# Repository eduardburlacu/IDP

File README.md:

# IDP

## Dimensions
- Truck Height: 95mm
- Tunnel Width: 345mm
- Tunnel Length: 510mm
-

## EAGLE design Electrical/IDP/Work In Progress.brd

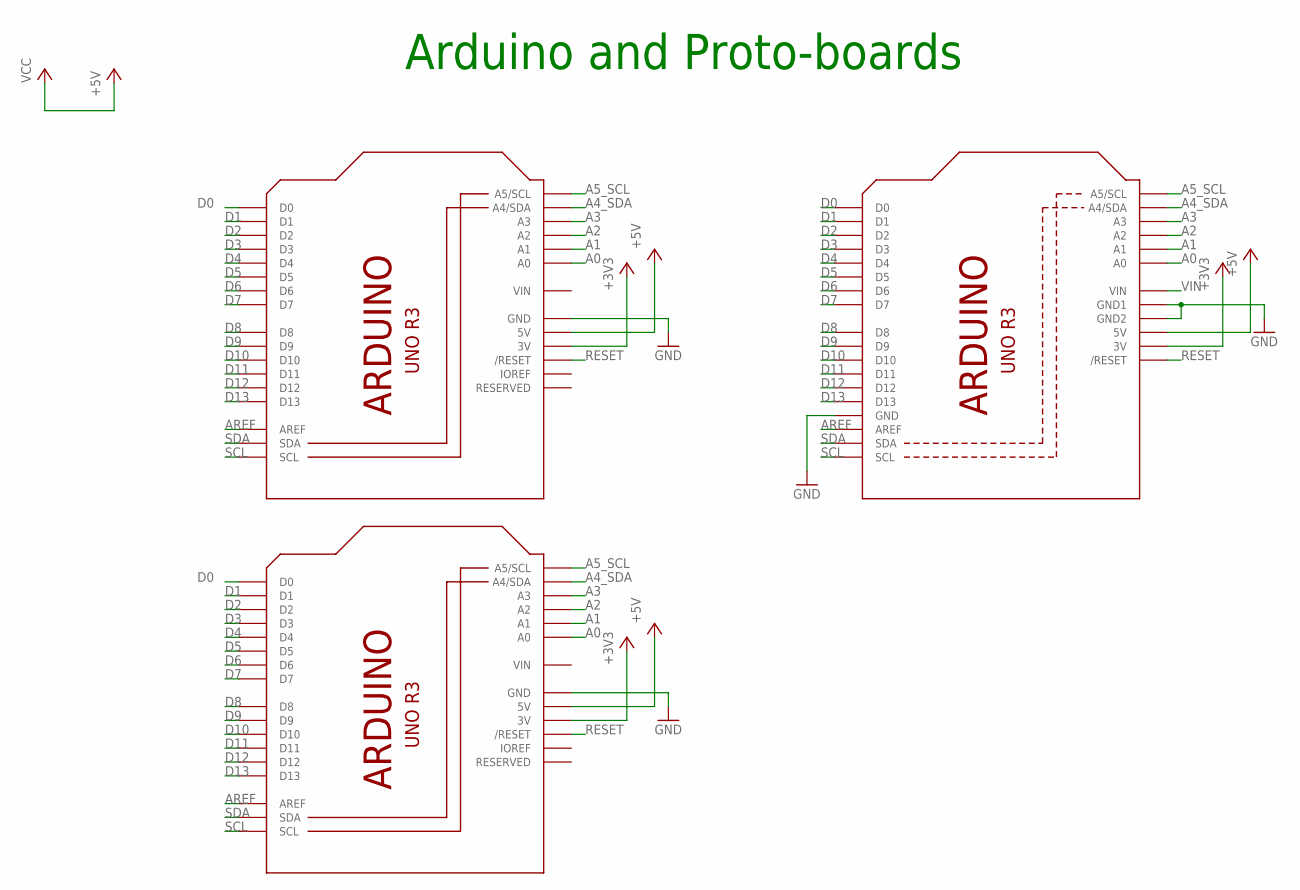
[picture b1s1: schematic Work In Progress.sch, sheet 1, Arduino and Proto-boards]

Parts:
M1, M2: IDP_PROTOBOARD_LARGE_LARGE; IDP_PROTO_LARGE
Q1: ARDUINOR3-NOIOREF-NOTEXT; ARDUINOR3-NOTEXT-NOIOREF

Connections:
+3V3: M1.3V, M2.3V, Q1.3V
+5V: M1.5V, M1.5V@0 (5V), M1.5V@1 (5V), M1.5V@2 (5V), M1.5V@3 (5V), M1.5V@4 (5V), M1.5V@5 (5V), M1.5V@6 (5V), M1.5V@7 (5V), M1.5V@8 (5V), M1.5V@9 (5V), M1.5V@10 (5V), M1.5V@11 (5V), M1.5V@12 (5V), M1.5V@13 (5V), M1.5V@14 (5V), M1.5V@15 (5V), M1.5V@16 (5V), M1.5V@17 (5V), M1.5V@18 (5V), M1.5V@19 (5V), M1.5V@20 (5V), M1.5V@21 (5V), M1.5V@22 (5V), M1.5V@23 (5V), M1.5V@24 (5V), M1.5V@25 (5V), M1.5V@26 (5V), M1.5V@27 (5V), M1.5V@28 (5V), M1.5V@29 (5V), M1.5V@30 (5V), M1.5V@31 (5V), M1.5V@32 (5V), M1.5V@33 (5V), M1.5V@34 (5V), M1.5V@35 (5V), M1.5V@36 (5V), M1.5V@37 (5V), M1.5V@38 (5V), M1.5V@39 (5V), M1.5V@40 (5V), M1.5V@41 (5V), M1.5V@42 (5V), M1.5V@43 (5V), M1.5V@44 (5V), M1.5V@45 (5V), M1.5V@46 (5V), M1.5V@47 (5V), M1.5V@48 (5V), M1.5V@49 (5V), M1.5V@50 (5V), M1.5V@51 (5V), M1.5V@52 (5V), M1.5V@53 (5V), M1.5V@54 (5V), M1.5V@55 (5V), M1.5V@56 (5V), M1.5V@57 (5V), M1.5V@58 (5V), M1.5V@59 (5V), M1.5V@60 (5V), M1.5V@61 (5V), M1.5V@62 (5V), M1.5V@63 (5V), M1.5V@64 (5V), M1.5V@65 (5V), M1.5V@66 (5V), M1.5V@67 (5V), M1.5V@68 (5V), M1.5V@69 (5V), M1.5V@70 (5V), M2.5V, M2.5V@0 (5V), M2.5V@1 (5V), M2.5V@2 (5V), M2.5V@3 (5V), M2.5V@4 (5V), M2.5V@5 (5V), M2.5V@6 (5V), M2.5V@7 (5V), M2.5V@8 (5V), M2.5V@9 (5V), M2.5V@10 (5V), M2.5V@11 (5V), M2.5V@12 (5V), M2.5V@13 (5V), M2.5V@14 (5V), M2.5V@15 (5V), M2.5V@16 (5V), M2.5V@17 (5V), M2.5V@18 (5V), M2.5V@19 (5V), M2.5V@20 (5V), M2.5V@21 (5V), M2.5V@22 (5V), M2.5V@23 (5V), M2.5V@24 (5V), M2.5V@25 (5V), M2.5V@26 (5V), M2.5V@27 (5V), M2.5V@28 (5V), M2.5V@29 (5V), M2.5V@30 (5V), M2.5V@31 (5V), M2.5V@32 (5V), M2.5V@33 (5V), M2.5V@34 (5V), M2.5V@35 (5V), M2.5V@36 (5V), M2.5V@37 (5V), M2.5V@38 (5V), M2.5V@39 (5V), M2.5V@40 (5V), M2.5V@41 (5V), M2.5V@42 (5V), M2.5V@43 (5V), M2.5V@44 (5V), M2.5V@45 (5V), M2.5V@46 (5V), M2.5V@47 (5V), M2.5V@48 (5V), M2.5V@49 (5V), M2.5V@50 (5V), M2.5V@51 (5V), M2.5V@52 (5V), M2.5V@53 (5V), M2.5V@54 (5V), M2.5V@55 (5V), M2.5V@56 (5V), M2.5V@57 (5V), M2.5V@58 (5V), M2.5V@59 (5V), M2.5V@60 (5V), M2.5V@61 (5V), M2.5V@62 (5V), M2.5V@63 (5V), M2.5V@64 (5V), M2.5V@65 (5V), M2.5V@66 (5V), M2.5V@67 (5V), M2.5V@68 (5V), M2.5V@69 (5V), M2.5V@70 (5V), Q1.5V; also elsewhere on the board
A0: M1.A0, M2.A0, Q1.A0
A1: M1.A1, M2.A1, Q1.A1
A2: M1.A2, M2.A2, Q1.A2
A3: M1.A3, M2.A3, Q1.A3
A4_SDA: M1.A4 (A4/SDA), M2.A4 (A4/SDA), Q1.A4 (A4/SDA)
A5_SCL: M1.A5 (A5/SCL), M2.A5 (A5/SCL), Q1.A5 (A5/SCL)
AREF: M1.AREF, M2.AREF, Q1.AREF
D0: M1.D0, M2.D0, Q1.D0
D1: M1.D1, M2.D1, Q1.D1; also elsewhere on the board
D2: M1.D2, M2.D2, Q1.D2; also elsewhere on the board
D3: M1.D3, M2.D3, Q1.D3; also elsewhere on the board
D4: M1.D4, M2.D4, Q1.D4; also elsewhere on the board
D5: M1.D5, M2.D5, Q1.D5
D6: M1.D6, M2.D6, Q1.D6
D7: M1.D7, M2.D7, Q1.D7
D8: M1.D8, M2.D8, Q1.D8; also elsewhere on the board
D9: M1.D9, M2.D9, Q1.D9; also elsewhere on the board
D10: M1.D10, M2.D10, Q1.D10; also elsewhere on the board
D11: M1.D11, M2.D11, Q1.D11; also elsewhere on the board
D12: M1.D12, M2.D12, Q1.D12
D13: M1.D13, M2.D13, Q1.D13
GND: M1.GND, M1.GND1 (GND), M1.GND2 (GND), M1.GND3 (GND), M1.GND4 (GND), M1.GND5 (GND), M1.GND6 (GND), M1.GND7 (GND), M1.GND8 (GND), M1.GND9 (GND), M1.GND10 (GND), M1.GND11 (GND), M1.GND12 (GND), M1.GND13 (GND), M1.GND14 (GND), M1.GND15 (GND), M1.GND16 (GND), M1.GND17 (GND), M1.GND18 (GND), M1.GND19 (GND), M1.GND20 (GND), M1.GND21 (GND), M1.GND22 (GND), M1.GND23 (GND), M1.GND24 (GND), M1.GND25 (GND), M1.GND26 (GND), M1.GND27 (GND), M1.GND28 (GND), M1.GND29 (GND), M1.GND30 (GND), M1.GND31 (GND), M1.GND32 (GND), M1.GND33 (GND), M1.GND@1 (GND), M1.GND@2 (GND), M1.GND@3 (GND), M1.GND@4 (GND), M1.GND@5 (GND), M1.GND@6 (GND), M1.GND@7 (GND), M1.GND@8 (GND), M1.GND@9 (GND), M1.GND@10 (GND), M1.GND@11 (GND), M1.GND@12 (GND), M1.GND@13 (GND), M1.GND@14 (GND), M1.GND@15 (GND), M1.GND@16 (GND), M1.GND@17 (GND), M1.GND@26 (GND), M1.GND@27 (GND), M1.GND@28 (GND), M1.GND@29 (GND), M1.GND@30 (GND), M1.GND@31 (GND), M1.GND@32 (GND), M1.GND@33 (GND), M1.GND@34 (GND), M1.GND@35 (GND), M1.GND@36 (GND), M1.GND@37 (GND), M1.GND@38 (GND), M1.GND@39 (GND), M1.GND@40 (GND), M1.GND@41 (GND), M1.GND@42 (GND), M1.GND@43 (GND), M1.GND@44 (GND), M1.GND@45 (GND), M1.GND@46 (GND), M1.GND@47 (GND), M1.GND@48 (GND), M2.GND, M2.GND1 (GND), M2.GND2 (GND), M2.GND3 (GND), M2.GND4 (GND), M2.GND5 (GND), M2.GND6 (GND), M2.GND7 (GND), M2.GND8 (GND), M2.GND9 (GND), M2.GND10 (GND), M2.GND11 (GND), M2.GND12 (GND), M2.GND13 (GND), M2.GND14 (GND), M2.GND15 (GND), M2.GND16 (GND), M2.GND17 (GND), M2.GND18 (GND), M2.GND19 (GND), M2.GND20 (GND), M2.GND21 (GND), M2.GND22 (GND), M2.GND23 (GND), M2.GND24 (GND), M2.GND25 (GND), M2.GND26 (GND), M2.GND27 (GND), M2.GND28 (GND), M2.GND29 (GND), M2.GND30 (GND), M2.GND31 (GND), M2.GND32 (GND), M2.GND33 (GND), M2.GND@1 (GND), M2.GND@2 (GND), M2.GND@3 (GND), M2.GND@4 (GND), M2.GND@5 (GND), M2.GND@6 (GND), M2.GND@7 (GND), M2.GND@8 (GND), M2.GND@9 (GND), M2.GND@10 (GND), M2.GND@11 (GND), M2.GND@12 (GND), M2.GND@13 (GND), M2.GND@14 (GND), M2.GND@15 (GND), M2.GND@16 (GND), M2.GND@17 (GND), M2.GND@26 (GND), M2.GND@27 (GND), M2.GND@28 (GND), M2.GND@29 (GND), M2.GND@30 (GND), M2.GND@31 (GND), M2.GND@32 (GND), M2.GND@33 (GND), M2.GND@34 (GND), M2.GND@35 (GND), M2.GND@36 (GND), M2.GND@37 (GND), M2.GND@38 (GND), M2.GND@39 (GND), M2.GND@40 (GND), M2.GND@41 (GND), M2.GND@42 (GND), M2.GND@43 (GND), M2.GND@44 (GND), M2.GND@45 (GND), M2.GND@46 (GND), M2.GND@47 (GND), M2.GND@48 (GND), Q1.GND, Q1.GND1, Q1.GND2; also elsewhere on the board
RESET: M1.RESET (/RESET), M2.RESET (/RESET), Q1.RESET (/RESET)
SCL: M1.SCL, M2.SCL, Q1.SCL
SDA: M1.SDA, M2.SDA, Q1.SDA
VIN: Q1.VIN

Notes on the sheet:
Arduino and Proto-boards

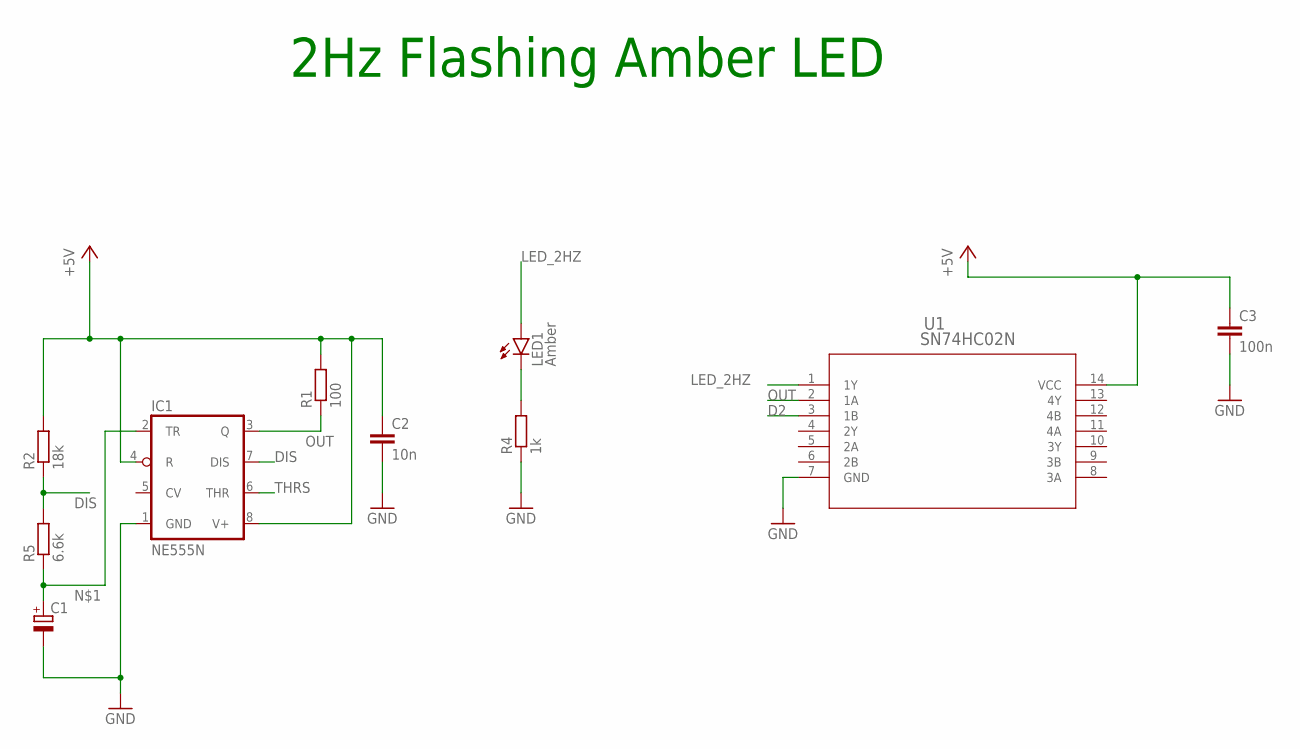
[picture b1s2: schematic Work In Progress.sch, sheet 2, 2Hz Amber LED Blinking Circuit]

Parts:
C1: CPOL-EUTT2D4; TT2D4
C2: 10n; C025-024X044
C3: 100n; C025-024X044
IC1: NE555N; DIL08-ROUND
LED1: Amber; LED3MM
R1: 100; 0204V
R2: 18k; 0204V
R4: 1k; 0204V
R5: 6.6k; 0204V
U1: SN74HC02N; N14

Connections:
+5V: C2.1, C3.1, IC1.4 (R), IC1.8 (V+), R1.2, R2.2, U1.14 (VCC); also elsewhere on the board
D2: U1.3 (1B); also elsewhere on the board
DIS: IC1.7 (DIS), R2.1, R5.2
GND: C1.-, C2.2, C3.2, IC1.1 (GND), R4.1, U1.7 (GND); also elsewhere on the board
LED_2HZ: LED1.A, U1.1 (1Y)
unnamed: C1.+, IC1.2 (TR), R5.1
unnamed: LED1.K (C), R4.2
OUT: IC1.3 (Q), R1.1, U1.2 (1A)
THRS: IC1.6 (THR)

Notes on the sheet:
2Hz Flashing Amber LED

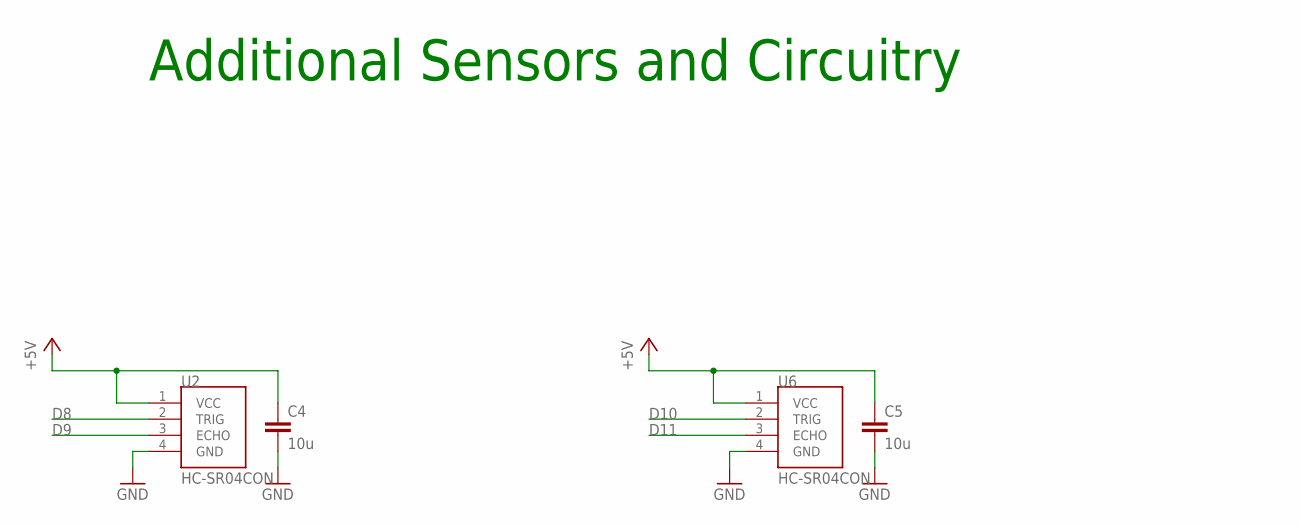
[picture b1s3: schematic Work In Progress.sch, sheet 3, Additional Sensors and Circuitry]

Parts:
C4, C5: 10u; C025-024X044
U2, U6: HC-SR04CON; 22-23-2041

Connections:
+5V: C4.1, C5.1, U2.1 (VCC), U6.1 (VCC); also elsewhere on the board
D8: U2.2 (TRIG); also elsewhere on the board
D9: U2.3 (ECHO); also elsewhere on the board
D10: U6.2 (TRIG); also elsewhere on the board
D11: U6.3 (ECHO); also elsewhere on the board
GND: C4.2, C5.2, U2.4 (GND), U6.4 (GND); also elsewhere on the board

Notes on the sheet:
Additional Sensors and Circuitry

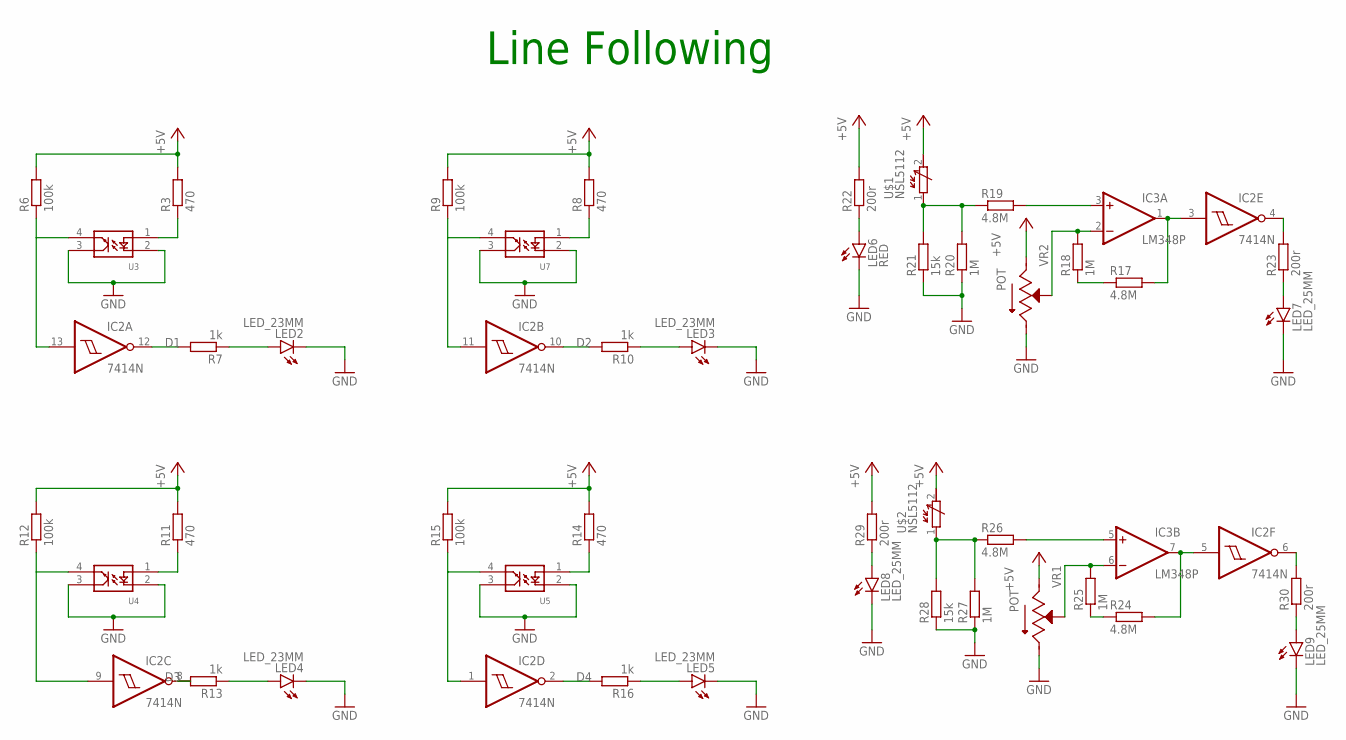
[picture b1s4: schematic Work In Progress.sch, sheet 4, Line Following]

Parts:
IC2: 7414N; DIL14
IC3: LM348P; DIL14
LED2, LED3, LED4, LED5: LED_23MM; LED3MM
LED6: RED; LED5MM
LED7, LED8, LED9: LED_25MM; LED5MM
R3, R8, R11, R14: 470; 0204V
R6, R9, R12, R15: 100k; 0204V
R7, R10, R13, R16: 1k; 0204V
R17, R19, R24, R26: 4.8M; 0204V
R18, R20, R25, R27: 1M; 0204V
R21, R28: 15k; 0204V
R22, R23, R29, R30: 200r; 0204V
U3, U4, U5, U7: OPB704; 22-23-2041
U$1, U$2: NSL5112; KK-156-2
VR1, VR2: POT; TRIM_3296W-1-250

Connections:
+5V: R3.2, R6.2, R8.2, R9.2, R11.2, R12.2, R14.2, R15.2, R22.2, R29.2, U$1.2 (E), U$2.2 (E), VR1.1 (CCW), VR2.1 (CCW); also elsewhere on the board
D1: IC2.12 (O), R7.2; also elsewhere on the board
D2: IC2.10 (O), R10.2; also elsewhere on the board
D3: IC2.8 (O), R13.2; also elsewhere on the board
D4: IC2.2 (O), R16.2; also elsewhere on the board
GND: IC2.7 (GND), LED2.K (C), LED3.K (C), LED4.K (C), LED5.K (C), LED6.K (C), LED7.K (C), LED8.K (C), LED9.K (C), R20.1, R21.1, R27.1, R28.1, U3.2 (1), U3.3, U4.2 (1), U4.3, U5.2 (1), U5.3, U7.2 (1), U7.3, VR1.3 (CW), VR2.3 (CW); also elsewhere on the board
unnamed: R3.1, U3.1 (2)
unnamed: LED2.A, R7.1
unnamed: IC2.13 (I), R6.1, U3.4
unnamed: R8.1, U7.1 (2)
unnamed: IC2.11 (I), R9.1, U7.4
unnamed: LED3.A, R10.1
unnamed: R11.1, U4.1 (2)
unnamed: IC2.9 (I), R12.1, U4.4
unnamed: LED4.A, R13.1
unnamed: R14.1, U5.1 (2)
unnamed: IC2.1 (I), R15.1, U5.4
unnamed: LED5.A, R16.1
unnamed: R17.1, R18.1
unnamed: IC2.3 (I), IC3.1 (OUT), R17.2
unnamed: IC3.2 (-IN), R18.2, VR2.2 (WIPER)
unnamed: IC3.3 (+IN), R19.2
unnamed: R19.1, R20.2, R21.2, U$1.1 (A)
unnamed: LED6.A, R22.1
unnamed: LED7.A, R23.1
unnamed: IC2.4 (O), R23.2
unnamed: R24.1, R25.1
unnamed: IC2.5 (I), IC3.7 (OUT), R24.2
unnamed: IC3.6 (-IN), R25.2, VR1.2 (WIPER)
unnamed: IC3.5 (+IN), R26.2
unnamed: R26.1, R27.2, R28.2, U$2.1 (A)
unnamed: LED8.A, R29.1
unnamed: LED9.A, R30.1
unnamed: IC2.6 (O), R30.2
V+: IC3.4 (V+)
V-: IC3.11 (V-)
VCC: IC2.14 (VCC)

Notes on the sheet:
Line Following

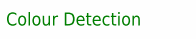
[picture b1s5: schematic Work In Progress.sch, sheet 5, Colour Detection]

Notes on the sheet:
Colour Detection

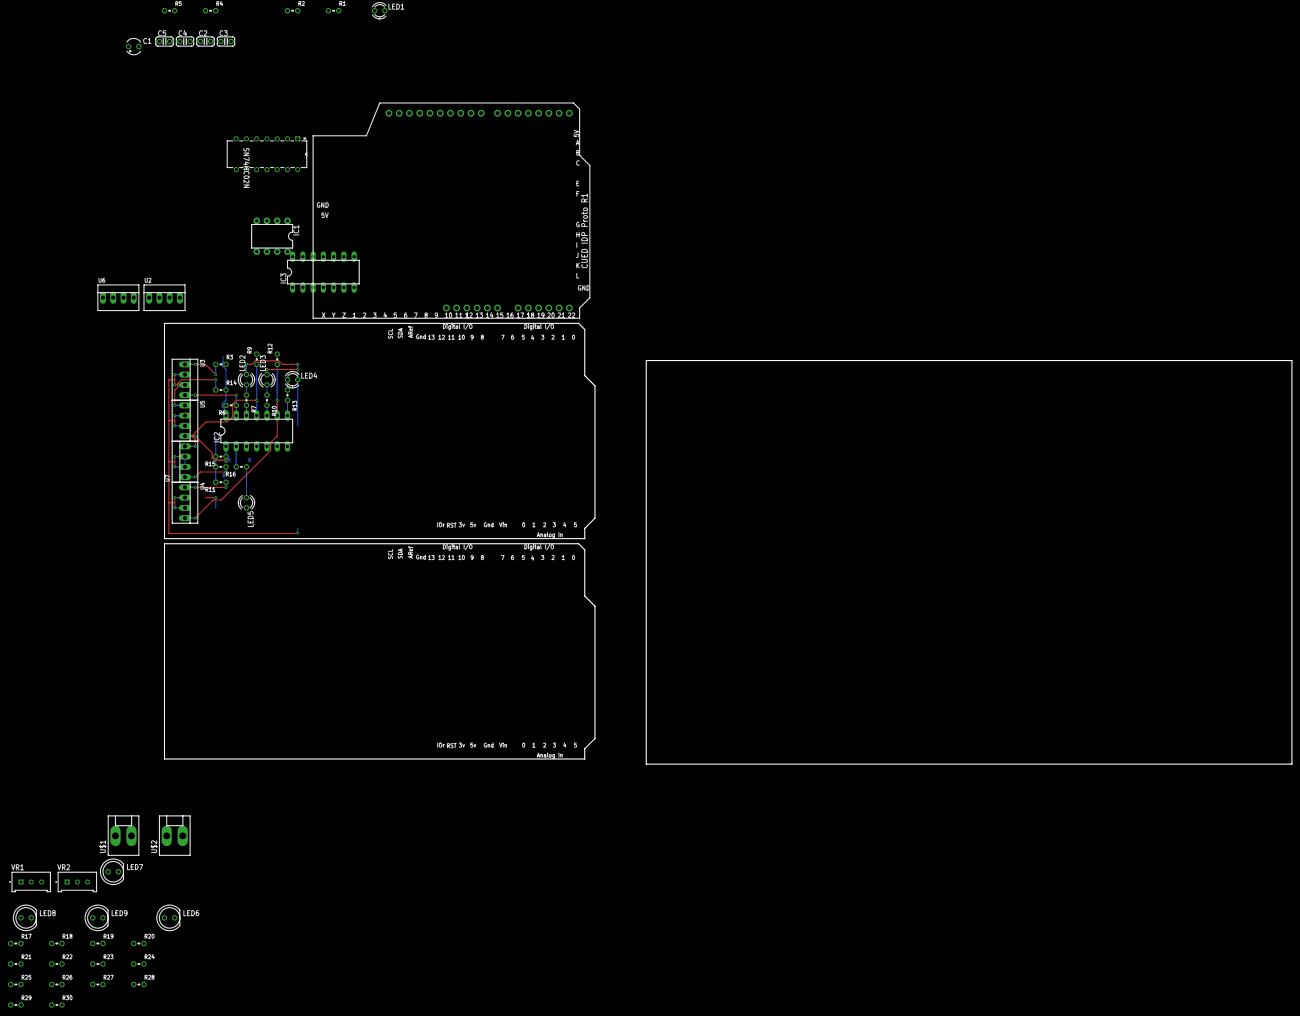
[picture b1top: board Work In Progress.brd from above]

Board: 2 copper layers, 279.4 x 109.2 mm, 61 parts (0 on the bottom side), 60 nets.

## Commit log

2023-01-17 Create c-cpp.yml
    To be used for the C++ test side
2023-01-17 Nothing really
2023-01-19 Added map dimensions
2023-01-19 Added Datasheets
2023-01-19 Added Project Documents
2023-01-19 Added Moodle Resources
2023-01-20 Added Gantt Chart
2023-01-20 Added Line Follower circuitry and schematic.
2023-01-20 Intro Presentation for Tuesday
    will need to add Gantt chart, more specific solutions for block elevation and navigation
2023-01-21 CodeVariables
2023-01-21 files+variables
2023-01-21 Added Ultrasonic Sensor code and schematic
2023-01-22 Added Circuits for Sharp 2Y0A02 IR Range Finder
2023-01-23 ADDED FLOWCHART
2023-01-23 added presentation v2.0
2023-01-23 Updated Ultrasonic Schematic capacitance
2023-01-23 Add files via upload
    Updated Flowchart
2023-01-23 Delete Introductory Presentation IDP.pptx
    Replacing with updated version
2023-01-23 Add files via upload
    Intro Presentation V3
2023-01-24 Added Schematic for NE555p timer circut for 2Hz operation
2023-01-26 Updated IR Range Finder schematic
2023-01-26 Added colour detector schematic
2023-01-26 Added timer schematic and updated eagle library
2023-01-26 Add files via upload
    This is the claw file. It is not fully finished as everything has not been fully mated but everything is in the right place.
2023-01-27 Claw pieces
2023-01-27 Mated Claw assembly and added block model
2023-01-27 Added solidworks models for claw
2023-01-27 Added circuit schematics
2023-01-29 SW v1.0 before testing and debugging
2023-01-29 StateChart added
2023-01-29 Tunnel detector by side sonar done
2023-01-30 Added IDP Eagle Project Folder
2023-01-31 Completed Line Follower routing
2023-01-31 code in a single file done
2023-01-31 added new line follower that rotates
    implemented similar to what Davit did today
2023-01-31 new line follower
    implemented like Davit's one in case the debugging for the pid is still not good
2023-01-31 Fixed bug related to comparison between char[] and uint8_t
2023-02-01 Added Simple Line Follower
2023-02-01 Working Line Follower
2023-02-02 New code for junction detection
    I added to yesterday's model a function that avoids the dodgy movement around junctions by setting l=0 every time ll=0 and same with r and rr.
2023-02-02 junction detection added
2023-02-02 junction detection + line following
2023-02-02 ADDED TURN STUFF
2023-02-08 Final code for competition1
2023-02-08 Updated code for COMPETITION1
2023-02-08 Moved pinMoving high signal to be when motors start
2023-02-08 Stopped loop failing after first call
2023-02-08 Altered logic in state 1 switch case
2023-02-08 Fixed logic in state 0 to prevent parking issues
2023-02-09 Competition code bug fixes
2023-02-09 Colour detector working
2023-02-13 Added Servo Testing Code
2023-02-13 update COMPETITION1
2023-02-14 FINAL!!!
2023-02-19 Rename junction detection added.ino to test_junction_detection
2023-02-19 Rename linesimple.ino to test_line_following
2023-02-19 Rename Servo Testing.ino to test_servos
2023-02-19 Rename Software/linesimple/test_line_following to Software/test_line_following
2023-02-19 Rename Software/Servo Testing/test_servos to Software/test_servos
2023-02-19 Rename Software/UnitTests/Motor Test/Motor Test.ino to Software/test_motors
2023-02-19 Rename Software/UnitTests/DCMotorsTogether/DCMotorsTogether.ino to Software/test_motors_together
2023-02-19 Rename Software/line/NEW_JUNCTION_TURN.ino to Software/test_junction_turns
2023-02-19 Rename Software/line - Copy/line - Copy.ino to Software/test_states_and_block_collection
2023-02-19 Rename Software/line/line.ino to Software/test_junction_states
2023-02-19 Rename Software/line/good_full.ino to Software/test_comprehensive
2023-02-19 Rename Software/line/header.h to Software/test_comprehensive_header
2023-02-19 Rename Software/test_comprehensive to Software/Testing/test_comprehensive
2023-02-19 Rename Software/test_comprehensive_header to Software/Testing/test_comprehensive_header
2023-02-19 Rename Software/test_junction_detection to Software/Testing/test_junction_detection
2023-02-19 Rename Software/test_junction_states to Software/Testing/test_junction_states
2023-02-19 Rename Software/test_junction_turns to Software/Testing/test_junction_turns
2023-02-19 Rename Software/test_line_following to Software/Testing/test_line_following
2023-02-19 Rename Software/test_motors to Software/Testing/test_motors
2023-02-19 Rename Software/test_motors_together to Software/Testing/test_motors_together
2023-02-19 Rename Software/test_servos to Software/Testing/test_servos
2023-02-19 Rename Software/test_states_and_block_collection to Software/Testing/test_states_and_block_collection
2023-02-19 Create placeholder
2023-02-19 Rename Software/COMPETITION1/final+/final+.ino to Software/final_competition
2023-02-19 Rename Software/COMPETITION1/COMPETITION1.ino to Software/first_competition
2023-02-20 Update final_competition
    Commenting and cleaning up code

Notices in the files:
parts and their libraries:
COPYRIGHT: Copyright (C) 2023 Ultra Librarian. All rights reserved.
